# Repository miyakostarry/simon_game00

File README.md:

# Simon -bread

A bread styled-shaped memory game made with a Raspberry Pi Pico.I added some twists so its not the same as the normal one.

## What is it?

The board lights up a led and plays a sound. You have to press the same button for that led back, in the same order. Every round the game adds one more led, so the pattern gets longer and longer and your brain gets more tired.

If you press the wrong led button, all the lights blink and you loose. If you remember 8 steps, you win and the middle led glowes you "won"

## My twists

- **Bread shaped PCB** - the board outline is made of round on one size, i drew it in KiCad. There is also a drawing on the back of the board.
- **Reverse mode** - a slide switch makes you press the pattern BACKWARDS. This is way harder then it sounds.
- **Centre LED** - it stays on in reverse mode so you dont forget wich mode your in, and it glows when you win.
- **Each petal has its own sound** - so you can almost play it like a tiny piano.

## How to play

1. Pick the mode with the slide switch BEFORE you start (one side is Classic, other side is Reverse).
2. Press any button to start.
3. Watch and listen to the pattern.
4. Press the button back. In Classic mode its the same order, in Reverse mode its backwards.
5. Get 8 right to win. Press a wrong one and you loose.

Example: the game shows red, blue, green.
- Classic: you press red, blue, green.
- Reverse: you press green, blue, red.

## Parts

| Part | How many |
|---|---|
| Raspberry Pi Pico (with headers) | 1 |
| 6mm push buttons | 4 |
| 5mm LEDs | 5 (4 petals + 1 centre) |
| 220 ohm resistors | 5 for the LEDs, plus a spare one for the buzzer |
| Passive buzzer (12mm) | 1 |
| SPDT slide switch | 1 |

The code is in the `firmware` folder. To use it:

1. Install Arduino IDE and add the Raspberry Pi Pico board package (the one by Earle Philhower).
2. Choose the board "Raspberry Pi Pico".
3. Hold BOOTSEL, plug in the Pico, and click Upload.

Status: the code is written and compiles, but i have not tested it on the real board yet because im still waiting for the parts and PCB. So there might be bugs, sorry in advance.

## Folders

- `kicad_simon` - the KiCad schematic and PCB
- `gerbers` - the files for the PCB factory
- `firmware` - the Arduino code
- `screenshots` - pictures of the schematic, PCB and 3D view

MADE FOR HACK CLUB HAFF-LIFE

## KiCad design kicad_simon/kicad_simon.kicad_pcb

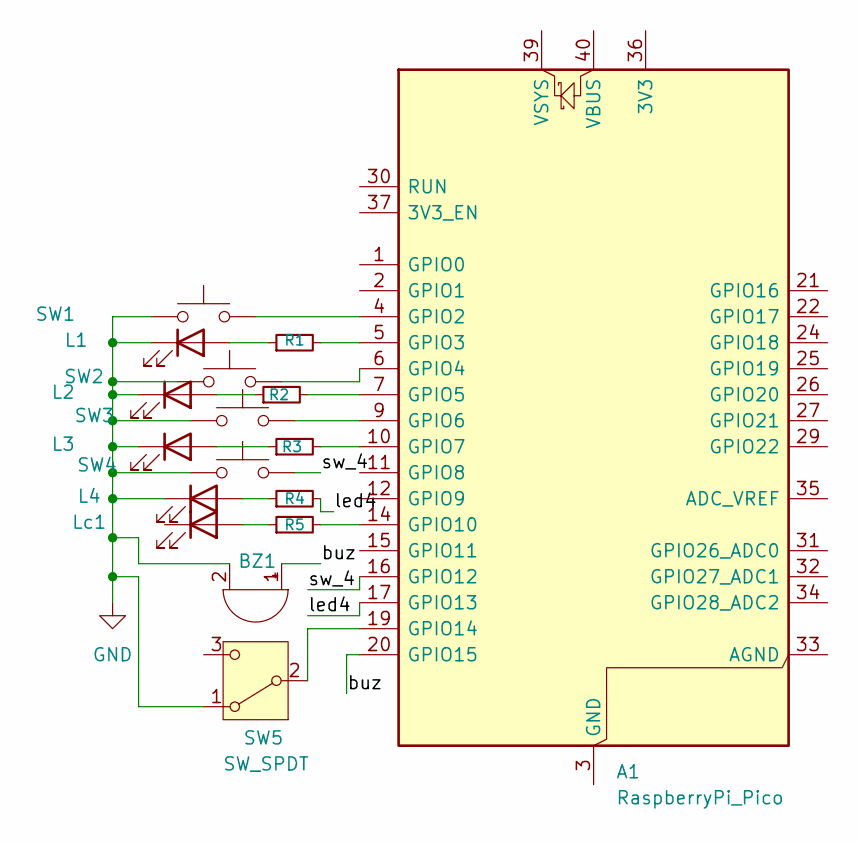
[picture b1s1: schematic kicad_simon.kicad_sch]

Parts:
A1: RaspberryPi_Pico; RaspberryPi_Pico_Common_THT
BZ1: Buzzer; Buzzer_12x9.5RM7.6
L1, L2, L3, L4: LED; LED_D5.0mm
Lc1: LED; LED_D5.0mm
R1, R2, R3, R4, R5: R_Small; R_Axial_DIN0207_L6.3mm_D2.5mm_P7.62mm_Horizontal
SW1, SW2, SW3, SW4: SW_Push; SW_PUSH_6mm
SW5: SW_SPDT; SW_Slide_SPDT_Straight_CK_OS102011MS2Q

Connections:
/buz: A1.20 (GPIO15), BZ1.1 (+)
/led4: A1.17 (GPIO13), R4.2
/sw_4: A1.16 (GPIO12), SW4.2
GND: BZ1.2 (-), L1.1 (K), L2.1 (K), L3.1 (K), L4.1 (K), SW1.1, SW2.1, SW3.1, SW4.1, SW5.1 (A)
unnamed: A1.3 (GND), A1.8 (GND), A1.13 (GND), A1.18 (GND), A1.23 (GND), A1.28 (GND), A1.38 (GND)
unnamed: A1.4 (GPIO2), SW1.2
unnamed: A1.5 (GPIO3), R1.2
unnamed: A1.6 (GPIO4), SW2.2
unnamed: A1.7 (GPIO5), R2.2
unnamed: A1.9 (GPIO6), SW3.2
unnamed: A1.10 (GPIO7), R3.2
unnamed: A1.14 (GPIO10), R5.2
unnamed: A1.19 (GPIO14), SW5.2 (B)
unnamed: L1.2 (A), R1.1
unnamed: L2.2 (A), R2.1
unnamed: L3.2 (A), R3.1
unnamed: L4.2 (A), R4.1
unnamed: Lc1.2 (A_2), R5.1

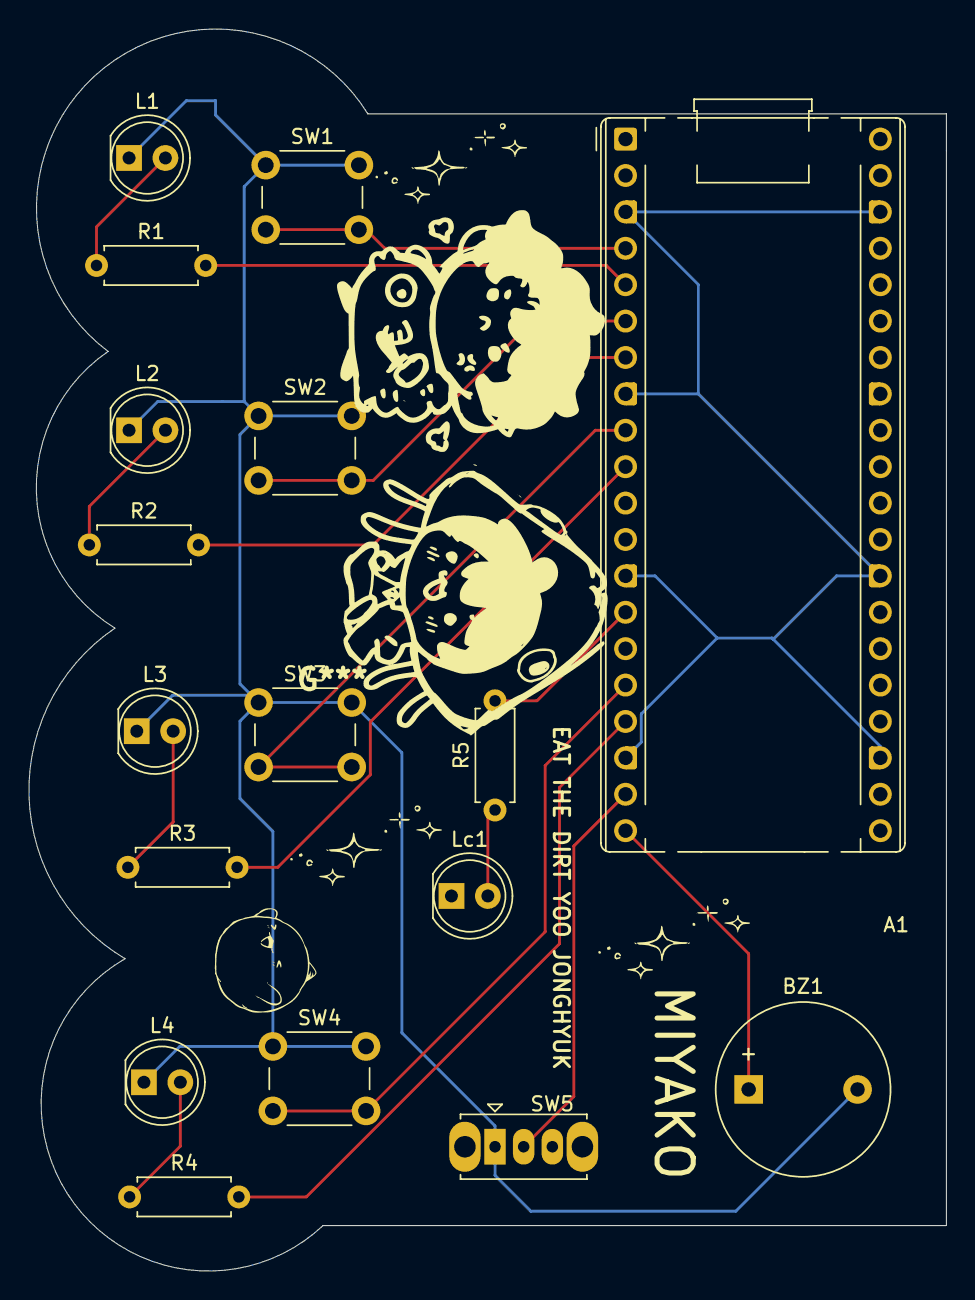
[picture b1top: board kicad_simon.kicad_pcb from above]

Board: 2 copper layers, 64.0 x 86.7 mm, 17 parts (0 on the bottom side), 18 nets.
